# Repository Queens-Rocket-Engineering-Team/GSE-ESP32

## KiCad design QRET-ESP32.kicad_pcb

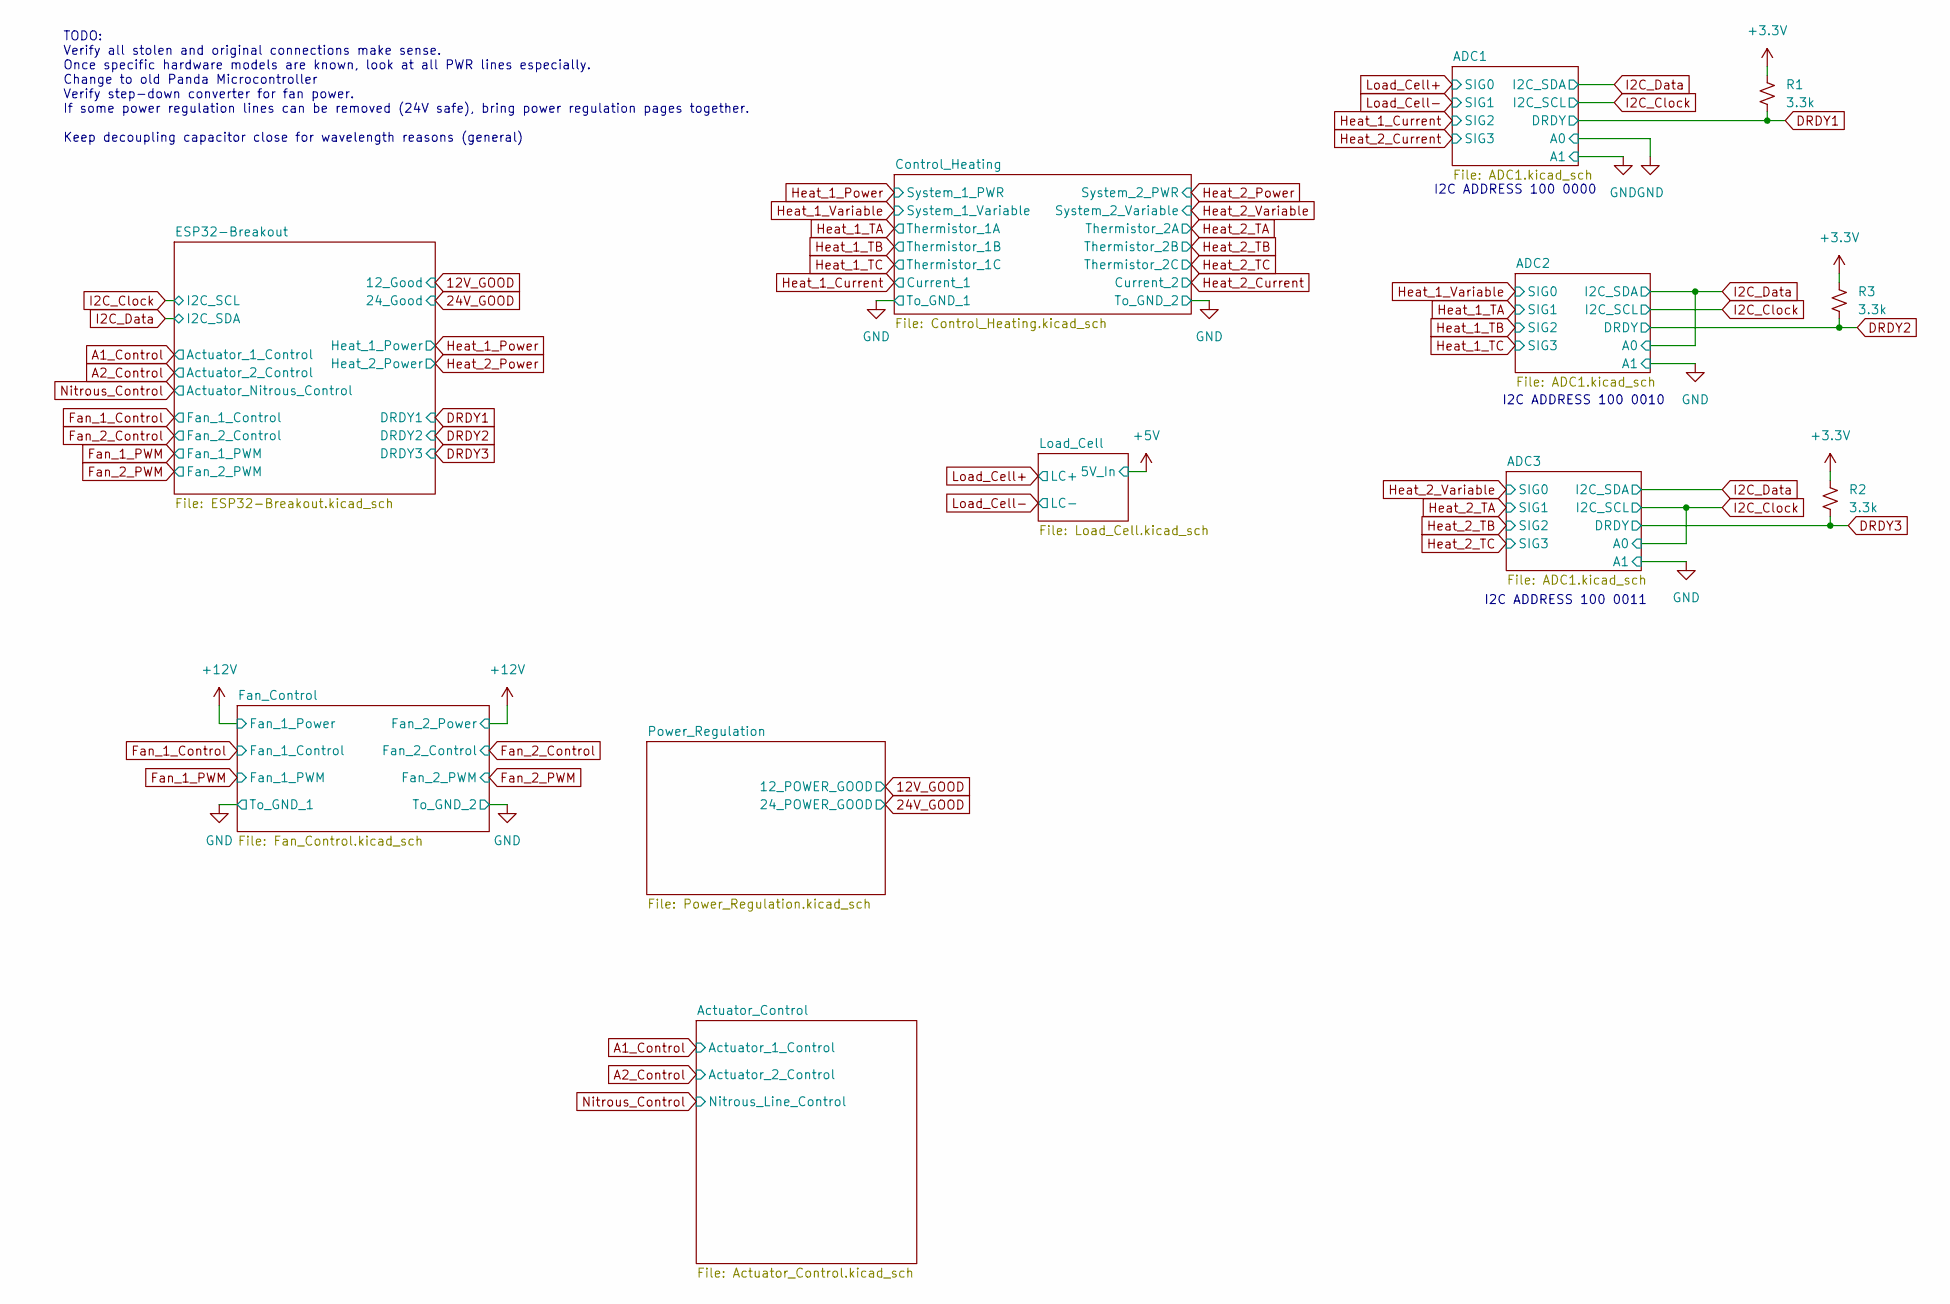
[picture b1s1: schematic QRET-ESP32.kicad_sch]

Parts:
R1, R2, R3: 3.3k; R_0402_1005Metric

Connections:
DRDY1: R1.2; also elsewhere on the board
DRDY2: R3.2; also elsewhere on the board
DRDY3: R2.2; also elsewhere on the board

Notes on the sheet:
TODO: Verify all stolen and original connections make sense. Once specific hardware models are known, look at all PWR lines especially. Change to old Panda Microcontroller Verify step-down converter for fan power. If some power regulation lines can be removed (24V safe), bring power regulation page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
I2C ADDRESS 100 0000
I2C ADDRESS 100 0011
I2C ADDRESS 100 0010

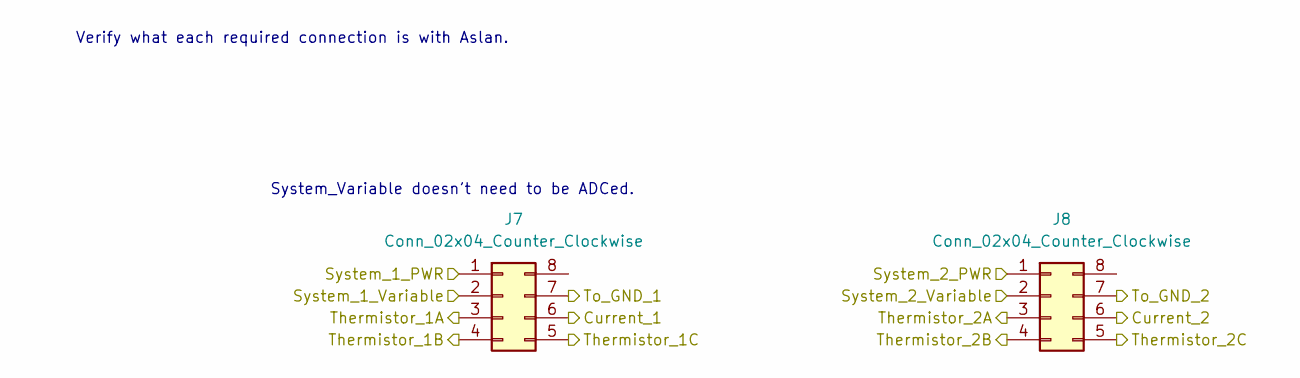
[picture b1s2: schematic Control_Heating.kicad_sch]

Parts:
J7, J8: Conn_02x04_Counter_Clockwise; JST_J2100_B08B-J21DK-GGXR_2x04_P2.50x4.00mm_Vertical

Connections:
Heat_1_Current: J7.6; also elsewhere on the board
Heat_1_Power: J7.1; also elsewhere on the board
Heat_1_TA: J7.3; also elsewhere on the board
Heat_1_TB: J7.4; also elsewhere on the board
Heat_1_TC: J7.5; also elsewhere on the board
Heat_1_Variable: J7.2; also elsewhere on the board
Heat_2_Current: J8.6; also elsewhere on the board
Heat_2_Power: J8.1; also elsewhere on the board
Heat_2_TA: J8.3; also elsewhere on the board
Heat_2_TB: J8.4; also elsewhere on the board
Heat_2_TC: J8.5; also elsewhere on the board
Heat_2_Variable: J8.2; also elsewhere on the board

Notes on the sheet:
Verify what each required connection is with Aslan.
System_Variable doesn't need to be ADCed.

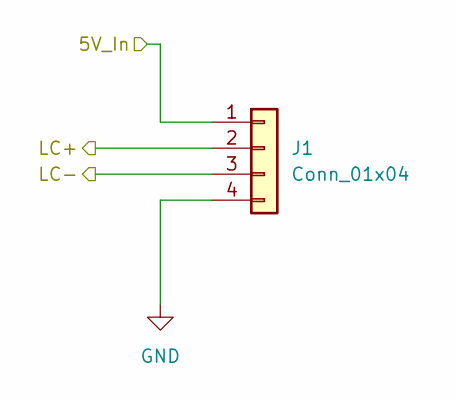
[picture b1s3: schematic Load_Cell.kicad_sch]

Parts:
J1: Conn_01x04; JST_EH_B4B-EH-A_1x04_P2.50mm_Vertical

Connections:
+5V: J1.1; also elsewhere on the board
Load_Cell+: J1.2; also elsewhere on the board
Load_Cell-: J1.3; also elsewhere on the board

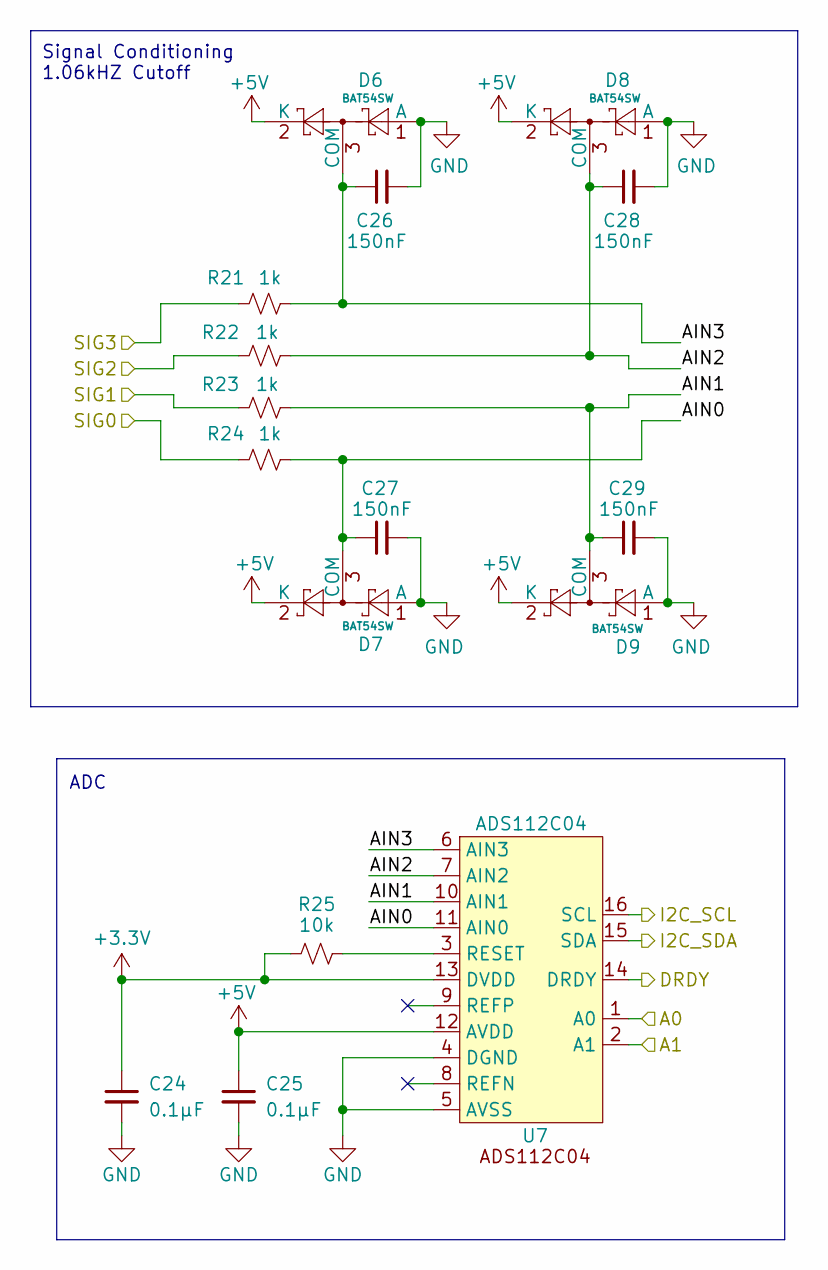
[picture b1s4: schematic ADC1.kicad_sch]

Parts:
C24, C25: 0.1μF; C_0402_1005Metric; MPN CL05B104KO5NNNC; LCSC C307331
C26, C27, C28, C29: 150nF; C_0402_1005Metric; LCSC C576725
D6, D7, D8, D9: BAT54SW; SOT-323_SC-70; LCSC C83575
R21, R22, R23, R24: 1k; R_0402_1005Metric
R25: 10k; R_0402_1005Metric; MPN 0402WGJ0103TCE; LCSC C25531
U7: ADS112C04; TSSOP-16_4.4x5mm_P0.65mm; MPN ADS112C04IPWR; LCSC C701615

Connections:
+5V: C25.1, D6.2 (K), D7.2 (K), D8.2 (K), D9.2 (K), U7.12 (AVDD); also elsewhere on the board
/ADC1/AIN0: C27.1, D7.3 (COM), R24.2, U7.11 (AIN0)
/ADC1/AIN1: C29.1, D9.3 (COM), R23.2, U7.10 (AIN1)
/ADC1/AIN2: C28.1, D8.3 (COM), R22.2, U7.7 (AIN2)
/ADC1/AIN3: C26.1, D6.3 (COM), R21.2, U7.6 (AIN3)
DRDY1: U7.14 (DRDY); also elsewhere on the board
Heat_1_Current: R22.1; also elsewhere on the board
Heat_2_Current: R21.1; also elsewhere on the board
I2C_Clock: U7.16 (SCL); also elsewhere on the board
I2C_Data: U7.15 (SDA); also elsewhere on the board
Load_Cell+: R24.1; also elsewhere on the board
Load_Cell-: R23.1; also elsewhere on the board
unnamed: R25.2, U7.3 (RESET)

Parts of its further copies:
C30, C31, C36, C37: 0.1μF; C_0402_1005Metric; MPN CL05B104KO5NNNC; LCSC C307331
C32, C33, C34, C35, C38, C39, C40, C41: 150nF; C_0402_1005Metric; LCSC C576725
D10, D11, D12, D13, D14, D15, D16, D17: BAT54SW; SOT-323_SC-70; LCSC C83575
R26, R27, R28, R29, R31, R32, R33, R34: 1k; R_0402_1005Metric
R30, R35: 10k; R_0402_1005Metric; MPN 0402WGJ0103TCE; LCSC C25531
U8, U9: ADS112C04; TSSOP-16_4.4x5mm_P0.65mm; MPN ADS112C04IPWR; LCSC C701615

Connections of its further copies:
+5V: C31.1, C37.1, D10.2 (K), D11.2 (K), D12.2 (K), D13.2 (K), D14.2 (K), D15.2 (K), D16.2 (K), D17.2 (K), U8.12 (AVDD), U9.12 (AVDD); also elsewhere on the board
/ADC2/AIN0: C33.1, D11.3 (COM), R29.2, U8.11 (AIN0)
/ADC2/AIN1: C35.1, D13.3 (COM), R28.2, U8.10 (AIN1)
/ADC2/AIN2: C34.1, D12.3 (COM), R27.2, U8.7 (AIN2)
/ADC2/AIN3: C32.1, D10.3 (COM), R26.2, U8.6 (AIN3)
/ADC3/AIN0: C39.1, D15.3 (COM), R34.2, U9.11 (AIN0)
/ADC3/AIN1: C41.1, D17.3 (COM), R33.2, U9.10 (AIN1)
/ADC3/AIN2: C40.1, D16.3 (COM), R32.2, U9.7 (AIN2)
/ADC3/AIN3: C38.1, D14.3 (COM), R31.2, U9.6 (AIN3)
DRDY2: U8.14 (DRDY); also elsewhere on the board
DRDY3: U9.14 (DRDY); also elsewhere on the board
Heat_1_TA: R28.1; also elsewhere on the board
Heat_1_TB: R27.1; also elsewhere on the board
Heat_1_TC: R26.1; also elsewhere on the board
Heat_1_Variable: R29.1; also elsewhere on the board
Heat_2_TA: R33.1; also elsewhere on the board
Heat_2_TB: R32.1; also elsewhere on the board
Heat_2_TC: R31.1; also elsewhere on the board
Heat_2_Variable: R34.1; also elsewhere on the board
I2C_Clock: U8.16 (SCL), U9.1 (A0), U9.16 (SCL); also elsewhere on the board
I2C_Data: U8.1 (A0), U8.15 (SDA), U9.15 (SDA); also elsewhere on the board
unnamed: R30.2, U8.3 (RESET)
unnamed: R35.2, U9.3 (RESET)

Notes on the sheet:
ADC
Signal Conditioning 1.06kHZ Cutoff

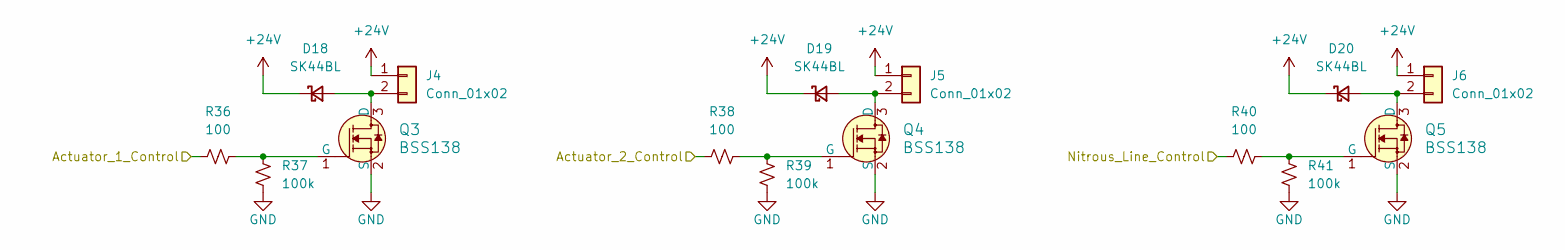
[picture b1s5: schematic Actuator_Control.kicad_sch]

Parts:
D18, D19, D20: SK44BL; D_SMB; MPN SK44BL-TP; LCSC C151740
J4, J5, J6: Conn_01x02; JST_EH_B2B-EH-A_1x02_P2.50mm_Vertical
Q3, Q4, Q5: BSS138; SOT-23-3; MPN BSS138; LCSC C8490
R36, R38, R40: 100; R_0402_1005Metric; MPN 0402WGF1000TCE; LCSC C25076
R37, R39, R41: 100k; R_0603_1608Metric; MPN 0402WGJ0104TCE; LCSC C25530

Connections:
+24V: D18.1 (K), D19.1 (K), D20.1 (K), J4.1, J5.1, J6.1; also elsewhere on the board
A1_Control: R36.1; also elsewhere on the board
A2_Control: R38.1; also elsewhere on the board
unnamed: D18.2 (A), J4.2, Q3.3 (D)
unnamed: D19.2 (A), J5.2, Q4.3 (D)
unnamed: D20.2 (A), J6.2, Q5.3 (D)
unnamed: Q3.1 (G), R36.2, R37.1
unnamed: Q4.1 (G), R38.2, R39.1
unnamed: Q5.1 (G), R40.2, R41.1
Nitrous_Control: R40.1; also elsewhere on the board

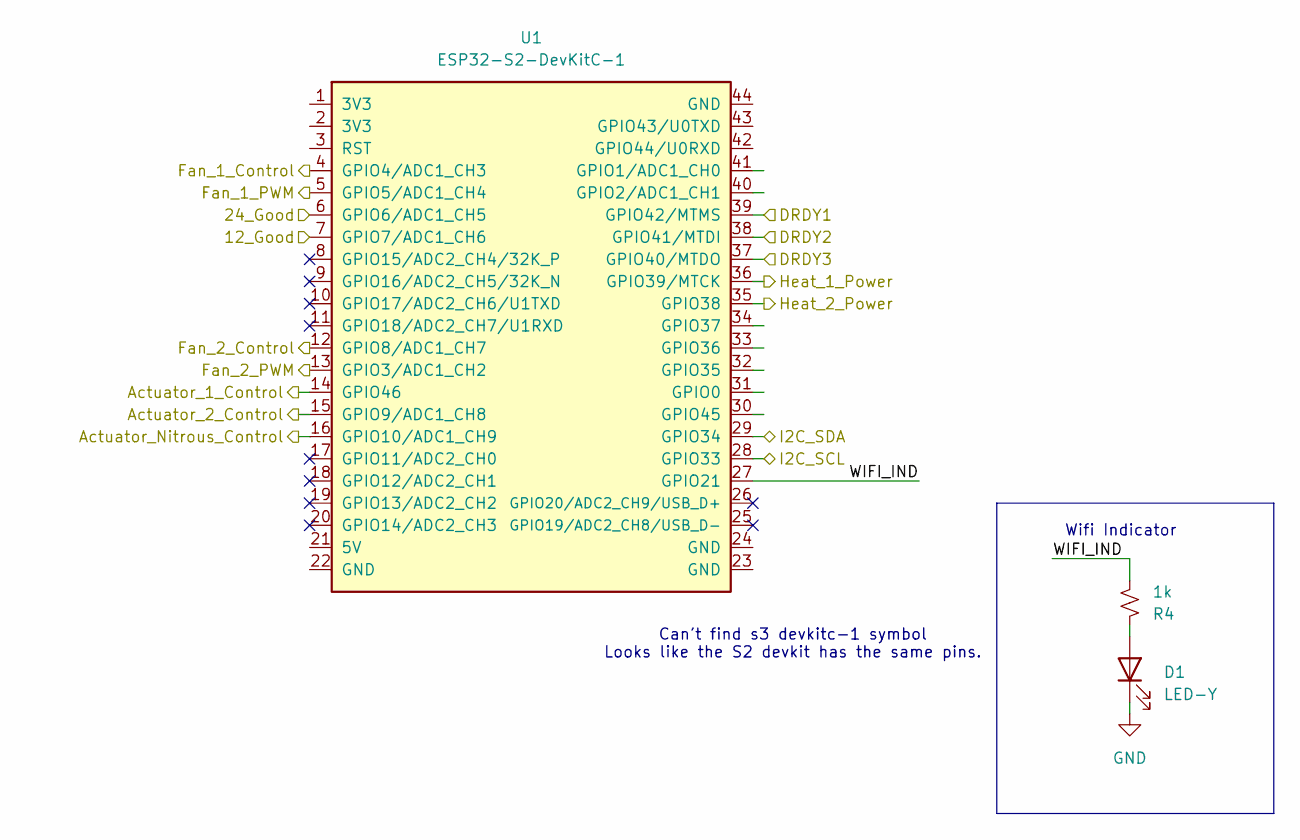
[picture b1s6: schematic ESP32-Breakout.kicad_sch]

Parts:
D1: LED-Y; LED_0805_2012Metric; LCSC C2296
R4: 1k; R_0402_1005Metric
U1: ESP32-S2-DevKitC-1

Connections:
12V_GOOD: U1.7 (GPIO7/ADC1_CH6); also elsewhere on the board
24V_GOOD: U1.6 (GPIO6/ADC1_CH5); also elsewhere on the board
/ESP32-Breakout/WIFI_IND: R4.2, U1.27 (GPIO21)
A1_Control: U1.14 (GPIO46); also elsewhere on the board
A2_Control: U1.15 (GPIO9/ADC1_CH8); also elsewhere on the board
DRDY1: U1.39 (GPIO42/MTMS); also elsewhere on the board
DRDY2: U1.38 (GPIO41/MTDI); also elsewhere on the board
DRDY3: U1.37 (GPIO40/MTDO); also elsewhere on the board
Fan_1_Control: U1.4 (GPIO4/ADC1_CH3); also elsewhere on the board
Fan_1_PWM: U1.5 (GPIO5/ADC1_CH4); also elsewhere on the board
Fan_2_Control: U1.12 (GPIO8/ADC1_CH7); also elsewhere on the board
Fan_2_PWM: U1.13 (GPIO3/ADC1_CH2); also elsewhere on the board
Heat_1_Power: U1.36 (GPIO39/MTCK); also elsewhere on the board
Heat_2_Power: U1.35 (GPIO38); also elsewhere on the board
I2C_Clock: U1.28 (GPIO33); also elsewhere on the board
I2C_Data: U1.29 (GPIO34); also elsewhere on the board
unnamed: D1.2 (A), R4.1
Nitrous_Control: U1.16 (GPIO10/ADC1_CH9); also elsewhere on the board

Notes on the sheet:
Can't find s3 devkitc-1 symbol Looks like the S2 devkit has the same pins.
Wifi Indicator

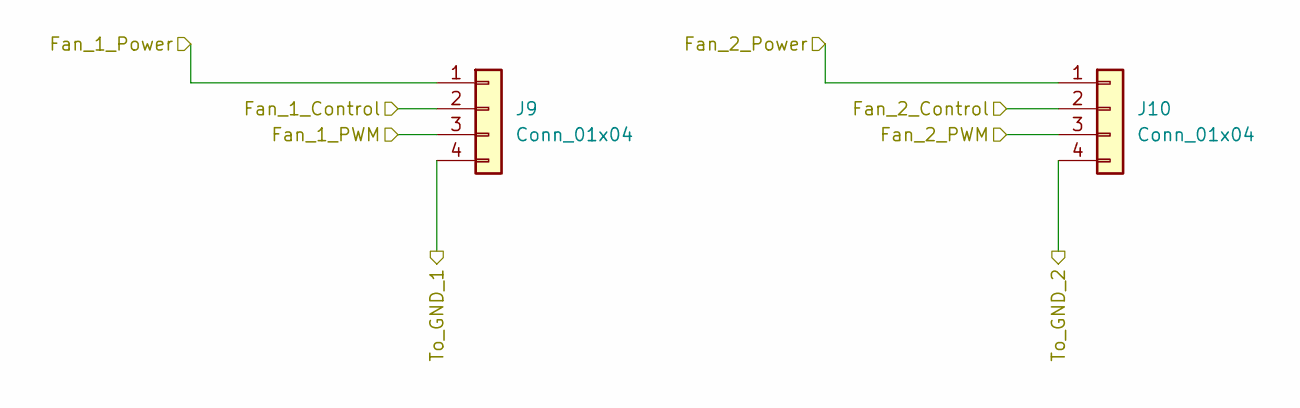
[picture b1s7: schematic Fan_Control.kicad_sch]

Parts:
J9, J10: Conn_01x04; JST_EH_B4B-EH-A_1x04_P2.50mm_Vertical

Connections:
+12V: J9.1, J10.1; also elsewhere on the board
Fan_1_Control: J9.2; also elsewhere on the board
Fan_1_PWM: J9.3; also elsewhere on the board
Fan_2_Control: J10.2; also elsewhere on the board
Fan_2_PWM: J10.3; also elsewhere on the board

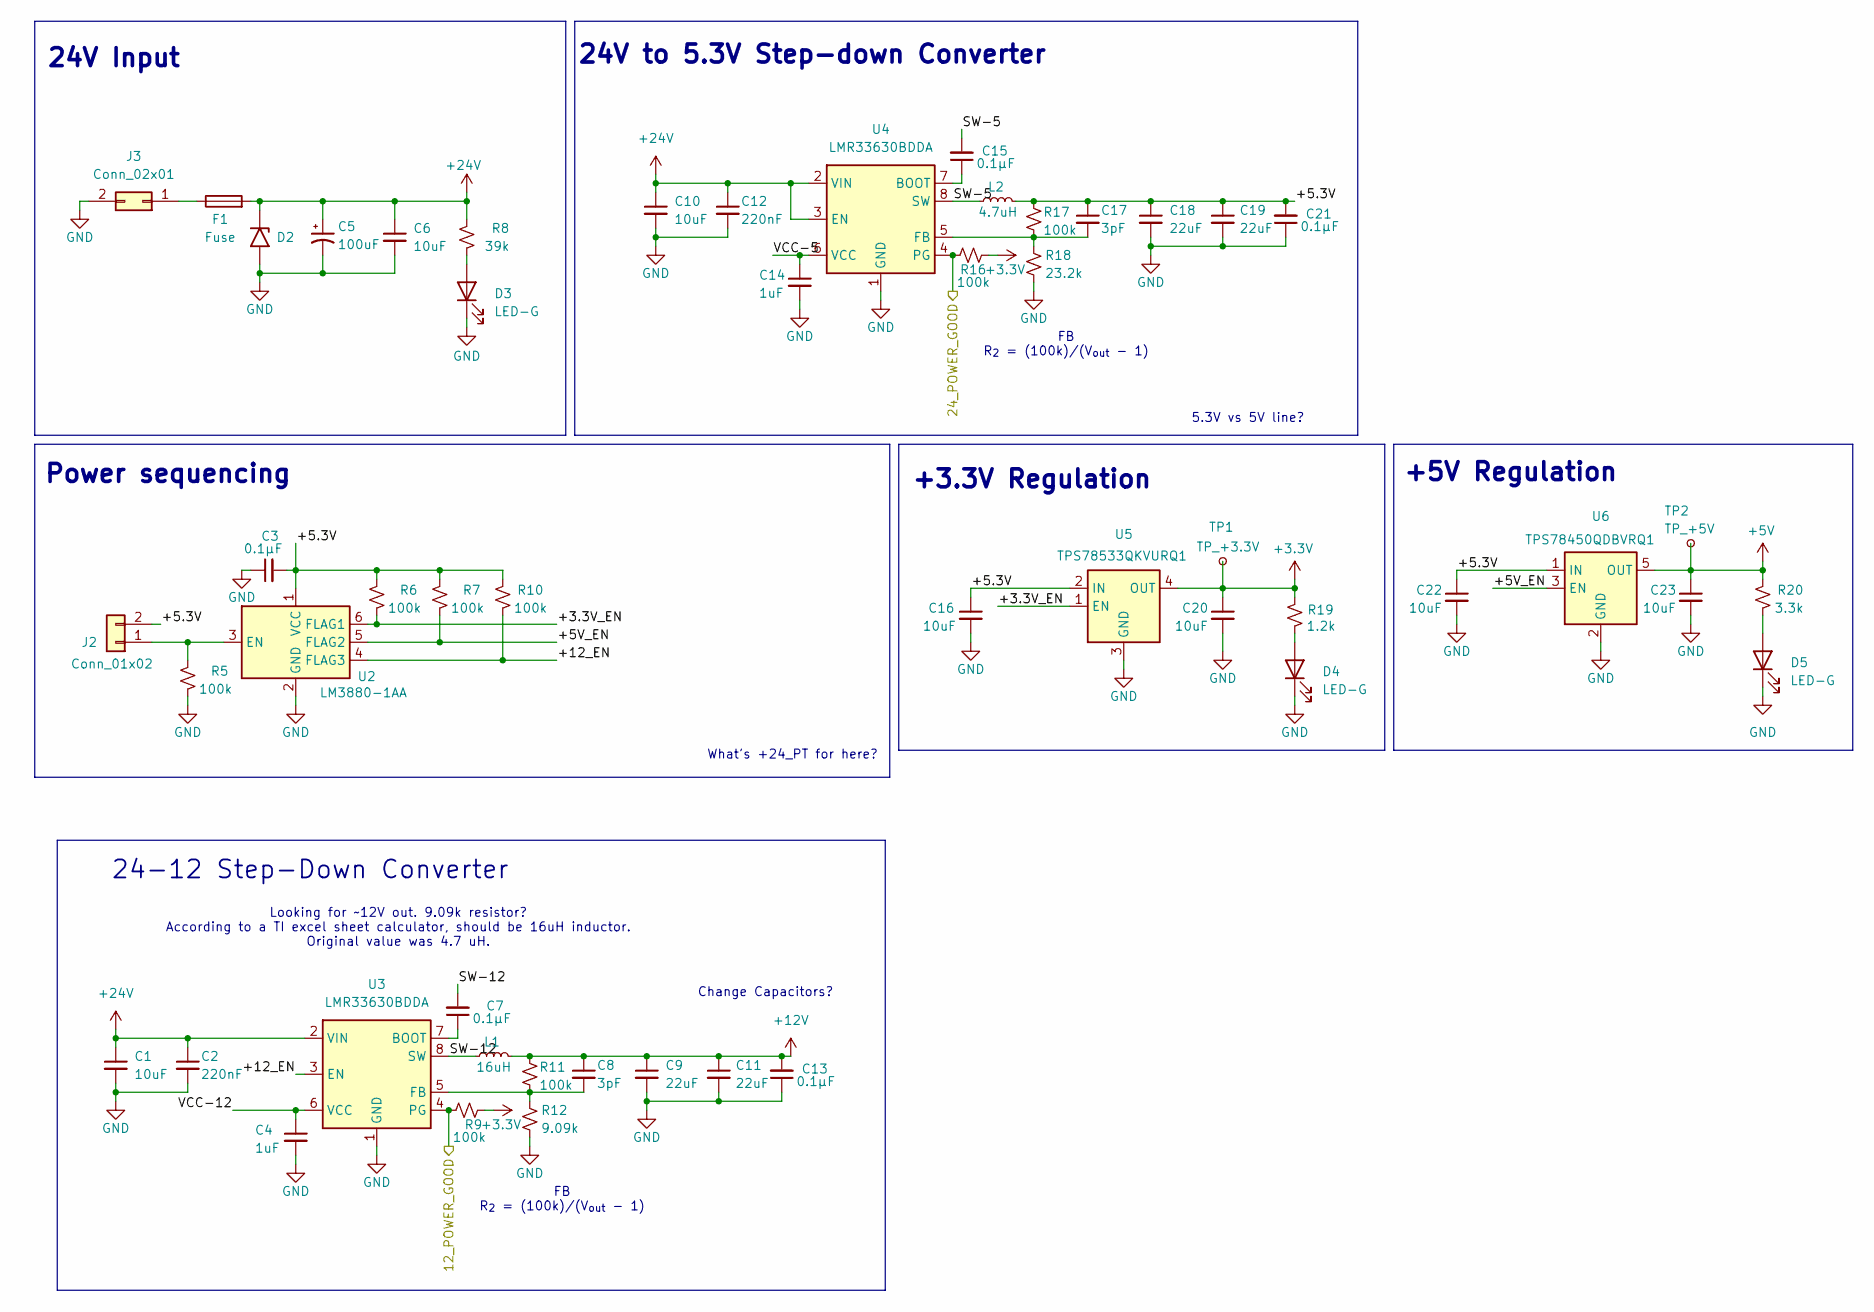
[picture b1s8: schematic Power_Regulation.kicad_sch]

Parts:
C1, C10: 10uF; C_1206_3216Metric; Voltage 50V; LCSC C13585
C2, C12: 220nF; C_0805_2012Metric; Voltage 50V; LCSC C5378
C3, C7, C13, C15, C21: 0.1μF; C_0402_1005Metric; MPN CL05B104KO5NNNC; LCSC C307331
C4, C14: 1uF; C_0603_1608Metric; LCSC C29936
C5: 100uF; CP_Elec_10x10; LCSC C161937
C6: 10uF; C_1812_4532Metric; Voltage 50V
C8, C17: 3pF; C_0603_1608Metric; LCSC C695157
C9, C11, C18, C19: 22uF; C_0805_2012Metric; LCSC C602037
C16, C20, C22, C23: 10uF; C_0805_2012Metric; LCSC C15850
D2: SMCJ26A-13-F; D_SMC; LCSC C135156
D3, D4, D5: LED-G; LED_0805_2012Metric; LCSC C2297
F1: Fuse; Fuseholder_Blade_Mini_Keystone_3568
J2: Conn_01x02; Molex_Micro-Fit_3.0_43650-0215_1x02_P3.00mm_Vertical
J3: Conn_02x01; Molex_Mini-Fit_Jr_5566-02A_2x01_P4.20mm_Vertical
L1: 16uH; L_Bourns_SRP7028A_7.3x6.6mm; LCSC C840529
L2: 4.7uH; L_Bourns_SRP7028A_7.3x6.6mm; LCSC C840529
R5, R6, R7, R10: 100k; R_0603_1608Metric
R8: 39k; R_0402_1005Metric
R9, R11, R16, R17: 100k; R_0603_1608Metric; MPN 0402WGJ0103TCE; LCSC C25531
R12: 9.09k; R_0603_1608Metric; MPN 0402WGF3301TCE; LCSC C25890
R18: 23.2k; R_0603_1608Metric; MPN 0402WGF3301TCE; LCSC C25890
R19: 1.2k; R_0402_1005Metric
R20: 3.3k; R_0402_1005Metric
TP1: TP_+3.3V; TestPoint_Pad_D1.0mm
TP2: TP_+5V; TestPoint_Pad_D1.0mm
U2: LM3880-1AA; SOT-23-6; LCSC C486059
U3, U4: LMR33630BDDA; Texas_HSOP-8-1EP_3.9x4.9mm_P1.27mm_ThermalVias; LCSC C544370
U5: TPS78533QKVURQ1; TO-252-4; LCSC C3748131
U6: TPS78450QDBVRQ1; SOT-23-5; LCSC C2877783

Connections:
12V_GOOD: R9.1, U3.4 (PG); also elsewhere on the board
24V_GOOD: R16.1, U4.4 (PG); also elsewhere on the board
+5V: C23.1, R20.2, TP2.1, U6.5 (OUT); also elsewhere on the board
+12V: C8.1, C9.1, C11.1, C13.2, L1.2, R11.1; also elsewhere on the board
+24V: C1.1, C2.1, C5.1, C6.1, C10.1, C12.1, D2.1 (A1), F1.2, R8.2, U3.2 (VIN), U4.2 (VIN), U4.3 (EN); also elsewhere on the board
/Power_Regulation/+3.3V_EN: R6.1, U2.6 (FLAG1), U5.1 (EN)
/Power_Regulation/+5.3V: C3.2, C16.1, C17.1, C18.1, C19.1, C21.2, C22.1, J2.2, L2.2, R6.2, R7.2, R10.2, R17.1, U2.1 (VCC), U5.2 (IN), U6.1 (IN)
/Power_Regulation/+5V_EN: R7.1, U2.5 (FLAG2), U6.3 (EN)
/Power_Regulation/+12_EN: R10.1, U2.4 (FLAG3), U3.3 (EN)
/Power_Regulation/SW-5: C15.2, L2.1, U4.8 (SW)
/Power_Regulation/SW-12: C7.2, L1.1, U3.8 (SW)
/Power_Regulation/VCC-5: C14.1, U4.6 (VCC)
/Power_Regulation/VCC-12: C4.1, U3.6 (VCC)
unnamed: D3.2 (A), R8.1
unnamed: D4.2 (A), R19.1
unnamed: D5.2 (A), R20.1
unnamed: J2.1, R5.2, U2.3 (EN)
unnamed: F1.1, J3.1
unnamed: C7.1, U3.7 (BOOT)
unnamed: C8.2, R11.2, R12.1, U3.5 (FB)
unnamed: C15.1, U4.7 (BOOT)
unnamed: C17.2, R17.2, R18.1, U4.5 (FB)

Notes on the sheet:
24V Input
5.3V vs 5V line?
24V to 5.3V Step-down Converter
What's +24_PT for here?
FB R_{2} = (100k)/(V_{out} - 1)
+3.3V Regulation
Change Capacitors?
Power sequencing
+5V Regulation
Looking for ~12V out. 9.09k resistor? According to a TI excel sheet calculator, should be 16uH inductor. Original value was 4.7 uH.
24-12 Step-Down Converter

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
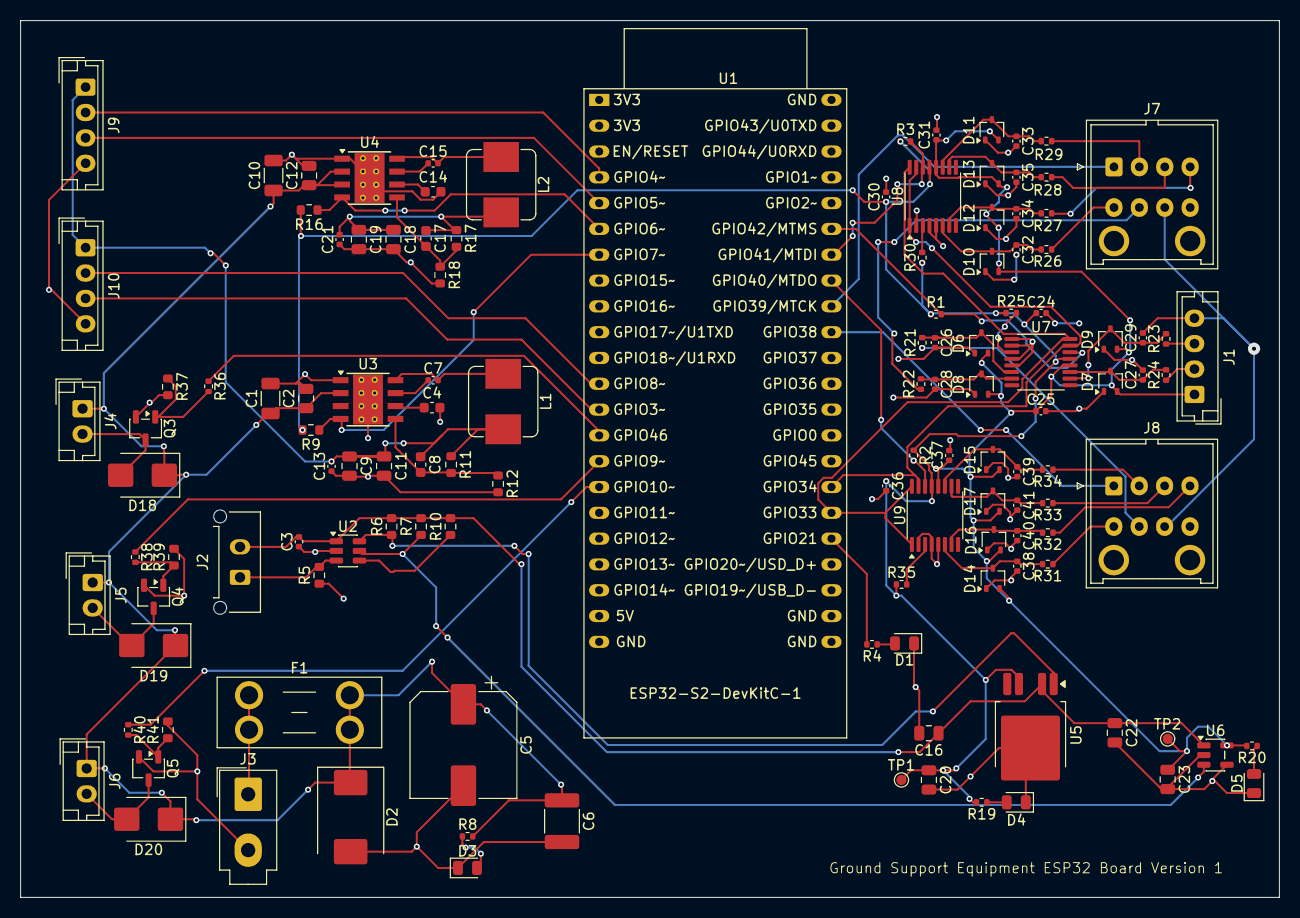
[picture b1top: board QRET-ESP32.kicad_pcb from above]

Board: 4 copper layers, 123.9 x 86.3 mm, 126 parts (0 on the bottom side), 73 nets.

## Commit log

2026-01-29 Stole a bunch more stuff from PANDA, added fan and heating line
2026-01-29 Actually included new files hopefully
2026-02-02 Updated most of root-page labels.
2026-02-06 Added 24V-12V step-down converter for fans, started switch to devkit.
2026-02-19 Updated to 4-pin fans, moved power pages together, deleted old reference.
2026-02-19 Removed unnecessary files.
2026-03-17 Started placement of ADC1 and 2.
2026-03-25 Adopted 4-layer setup and organized placement
2026-03-29 Initial PCB placement and wiring.
2026-04-01 Updated power regulation, To-Do: Rewire PCB
